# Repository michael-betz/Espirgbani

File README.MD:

# ESP Pinball RGB Animation clock

A LED-matrix clock, based on ESP32 and sprite_tm's I2S DMA driver.

__Note:__ 
the firmware here is outdated and will be removed in the future. 

[Espirgbani_pio](https://github.com/yetifrisstlama/espirgbani_pio) is up to date, has more features, less bugs, higher frame-rate and is much easier to build.

[Project log](http://yetifrisstlama.blogspot.com/2018/02/the-esp32-pinball-rgb-matrix-animation.html).

# PCB
Fits inside one of the 64x32 panels.

### Revisions
Changes included in Rev 1
  * Change programming port from custom pogo-pins to a normal header
  * Add input for ambient light level sensor
  * Re-arrange the mounting holes
  * Add second footprint for a uSD card

# Building
Unfortunately the projects which I based this software on are either completely obsolete or they moved on a lot. Building still works (as of April 2020) but only when using exactly the versions and git commits as specified below.

install [version 5.2.0 of `xtensa-esp32-elf` toolchain](https://dl.espressif.com/dl/xtensa-esp32-elf-linux64-1.22.0-80-g6c4433a-5.2.0.tar.gz) and put it in your `PATH`.

```bash
$ xtensa-esp32-elf-gcc --version
xtensa-esp32-elf-gcc (crosstool-NG crosstool-ng-1.22.0-80-g6c4433a) 5.2.0
Copyright (C) 2015 Free Software Foundation, Inc.
This is free software; see the source for copying conditions.  There is NO
warranty; not even for MERCHANTABILITY or FITNESS FOR A PARTICULAR PURPOSE.
```

install the esp-idf library.
```bash
git clone https://github.com/espressif/esp-idf.git
cd esp-idf
git checkout b173cf28174b17f7df96c298f83c16a00d22e312
git submodule init
git submodule update
cd components
git clone --recurse-submodules git@github.com:yetifrisstlama/libesphttpd.git
export IDF_PATH=<insert_path>/esp-idf
```

Clone Espirgbani, build and flash it ...

```bash
git clone git@github.com:yetifrisstlama/Espirgbani.git
cd Espirgbani/src
make
make flash     # program esp32 over serial port, hold the FLASH button!
make web-flash # program esp32 over wifi, set hostname in Makefile
```

## fast-seek
For a smoother animation playback, the fast-seek option needs to be enabled in
the fatfs library. Use the provided .patch file ...
```bash
cd esp-idf
patch -p1 -i ../Espirgbani/src/0001-Enable-FASTSEEK-option-in-FatFs.patch
```

# SD card instructions
Format as FAT32, then copy the following files:
  * `./settings.json`
  * `./runDmd.img`
  * `./fnt/{d}.fnt`
  * `./fnt/{d}_0.bmp`

## example `settings.json`
```json
{
    "panel": {
        "test_pattern": false,
        "tp_brightness":  10,
        "is_clk_inverted": true,
        "column_swap": false,
        "latch_offset": 0,
        "extra_blank": 1,
        "clkm_div_num": 4
    },
    "power": {
        "hi": {
            "h": 9,
            "m": 0,
            "p": 50,
            "pingIp": "192.168.1.208"
        },
        "lo": {
            "h": 22,
            "m": 45,
            "p": 1
        }
    },
    "delays": {
        "font":  60,
        "color": 10,
        "ani":   15,
        "ping":  60
    },
    "log_level": "W",
    "timezone": "PST8PDT,M3.2.0,M11.1.0",
    "hostname": "espirgbani",
    "wifis": {
        "<wifi-ssid>": {
            "pw": "<wifi-password>"
        }
    }
}
```
### `panel` section
Not all LED panels are the same. Here the timing parameters of the I2S panel driver can be configured.

  * `test_pattern`: if true, enters a LED panel test mode instead of normal operation
  * `tp_brightness`: brightness of the test pattern, from 1 to 127. Current draw gets ridiculous for the higher values
  * `is_clk_inverted`: if `false`, data changes on the rising clock edge. If `true`, data is stable on the rising clock edge (most panels need `true`)
  * `column_swap`: if true, swap each pair of vertical columns
  * when `latch_offset = 0`: latch row-data with last pixel. For positive / negative numbers the latching happens n clock cycles earlier / later. Shifts the image horizontally
  * `extra_blank` adds N additional delay cycles after latching before enabling the LEDs to prevent ghosting artifacts from one row to another
  * `clkm_div_num` sets the I2S clock divider from 1 to 128. Set it too high and get flicker,  too low get ghost pixels. `4` (= 8 MHz pixel clock) is a good compromise for my panels

### `power` section
controls the display brightness depending on current time.

  * Switches to brightness `90` at `9:00`
  * But only if `192.168.1.208` responds to pings
  * Switches to brightness `1` at `22:45`

### `delays` section
controls delays between random animations, color and font changes.

  * Changes the clock font every 60 minutes
  * Changes color of the clock font every 10 minutes
  * Plays a new pinball animation every 15 seconds
  * tries to ping `pingIp` every 60 seconds

### `log_level`
is the logging level for the serial port and the web-console on startup. Can be one of the following letters: `E = ERROR`, `W = WARN`, `I = INFO`, `D = DEBUG`, `V = VERBOSE`

### `timezone`
is the local timezone in [TZ format](https://www.gnu.org/software/libc/manual/html_node/TZ-Variable.html). Look it up [here](https://github.com/nayarsystems/posix_tz_db/blob/master/zones.csv).

Note that once running and connected to the wifi, the settings.json file can be edited through the web interface.

## how to get `runDmd.img`
  * Find a run-dmd image file and write it to SD card according to their instructions (HDD Raw Copy Tool and Windows required)
  * In linux, dump the first few hundred megabytes of the SD card to a file:
  ```bash
  sudo dd if=/dev/sdb of=./runDmd.img bs=1M count=125
  ```

## how to get the font `.bmp` and `.fnt` files
  * Find some nice fonts which look good at small size and copy the `.ttf` files into the git tree at `./dev/fonts`
  * Use [bmFont](http://www.angelcode.com/products/bmfont/) (works well with wine in linux) to generate the bitmap fonts. Good settings are provided in `dev/clockFont.bmfc`
    * Width: 52, Height: 2000
    * 32 bit per pixel (A = one, R = glyph, G = outline, B = zero)
    * .png texture file
    * binary .fnt descriptor file
    * Size: 30 px, Outline thickness: 1 px
  * Use imagemagick to convert all image files to bmp format
  * Rename them to 0_0.bmp, 0.fnt;  1_0.bmp, 1.fnt, ...
  * Alternatively, run `./dev/generateFonts.sh` which should automate these steps

## Pre-built binaries (TLDR!)
Prebuilt firmware binaries for the ESP32 and the files for the (FAT32) SD card are [here](https://github.com/yetifrisstlama/Espirgbani/releases/tag/v1.0).

# TODO
  * rewrite .json settings

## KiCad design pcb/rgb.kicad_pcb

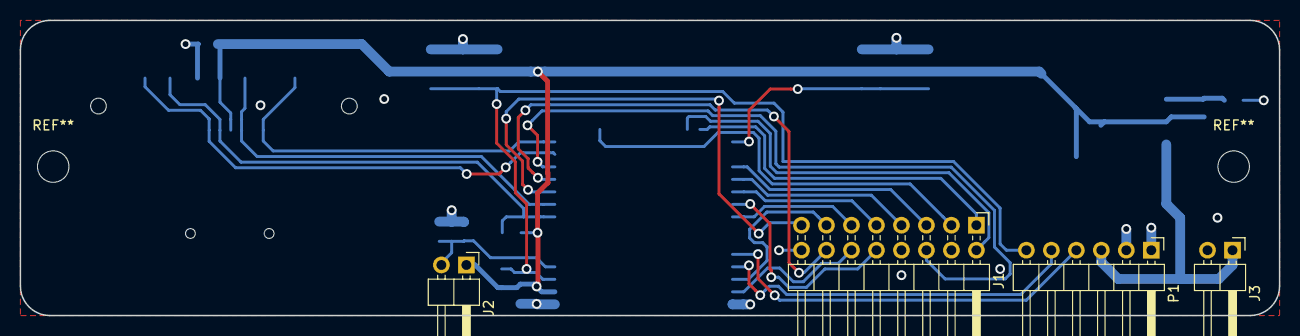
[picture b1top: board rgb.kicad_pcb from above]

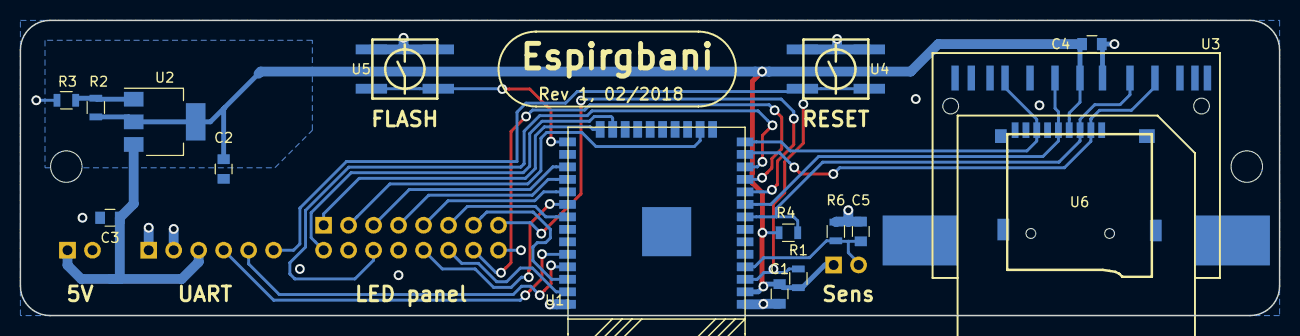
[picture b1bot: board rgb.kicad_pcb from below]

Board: 2 copper layers, 128.0 x 30.0 mm, 20 parts (16 on the bottom side), 26 nets.

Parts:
C1: 470n; C_0805
C2, C3, C4: 10u; C_0805
C5: 1u; C_0805
J1: Conn_02x08_Odd_Even; Pin_Header_Angled_2x08_Pitch2.54mm
J2, J3: Conn_01x02; Pin_Header_Angled_1x02_Pitch2.54mm
P1: TTL_232R_3V3; Pin_Header_Angled_1x06_Pitch2.54mm
R1: 470k; R_0805
R2: 590R; R_0805
R3: 1k; R_0805
R4, R6: 10k; R_0805
U1: ESP-WROOM-32
U2: REG1117; SOT-223
U3: 412D02F; RPIA_SD_CARD
U4, U5: TACTILE; EVQQ2
U6: MicroSD_SPI_CD; GCT-MEM2055-00-190-01-A

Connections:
+3V3: C1.2, C2.2, C4.1, J2.1, R1.1, R2.1, R4.2, U1.2, U2.2, U2.4, U3.7, U6.4
+5V: C3.2, J3.1, P1.3, U2.3
/A: J1.9, U1.29
/B: J1.10, U1.30
/B0: J1.3, U1.16
/B1: J1.7, U1.28
/C: J1.11, U1.31
/CLK: J1.13, U1.36
/D: J1.12, U1.37
/G0: J1.2, U1.23
/G1: J1.6, U1.12
/OE: J1.15, U1.10
/R0: J1.1, U1.24
/R1: J1.5, U1.27
/SD_CLK: U1.9, U3.8, U6.5
/SD_CS: U1.13, U3.4, U6.2
/SD_MISO: U1.14, U3.10, U6.7
/SD_MOSI: R4.1, U1.8, U3.5, U6.3
/STB: J1.14, U1.11
/progFlag: U1.25, U5.A, U5.A'
/rstBtn: P1.6, R1.2, U1.3, U4.A, U4.A'
GND: C1.1, C2.1, C3.1, C4.2, C5.2, J1.4, J1.8, J1.16, J3.2, P1.1, P1.2, R3.2, R6.2, U1.1, U1.15, U1.38, U1.39, U3.1, U3.2, U3.6, U3.9, U3.12, U3.13, U3.14, U3.15, U4.B, U4.B', U5.B, U5.B', U6.6
unnamed: C5.1, J2.2, R6.1, U1.4
unnamed: P1.4, U1.34
unnamed: P1.5, U1.35
unnamed: R2.2, R3.1, U2.1

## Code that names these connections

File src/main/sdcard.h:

#ifndef SDCARD_H
#define SDCARD_H

#define GPIO_SD_CLK  33
#define GPIO_SD_MOSI 32
#define GPIO_SD_MISO 12
#define GPIO_SD_CS   14

void initSd();

#endif

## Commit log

2017-11-30 Initial
2017-11-30 gitignore
2017-11-30 Readme
2017-12-01 Minimum example to show 1 (sub)frame for debugging
2017-12-03 First working version. MAtrix flickers when i2s clock si changed for bitplanes=7
2017-12-04 SD card is online and integrated into webserver
2017-12-04 Hmm sd card write bug?
2017-12-07 revengwork
2017-12-07 Got the gif extractor working
2017-12-08 Progress on file format
2017-12-08 offsets still a mystery
2017-12-08 Finally cracked the header offset
2017-12-08 c parser for header
2017-12-10 Finally cracked the header format with the correct offsets
2017-12-11 Animations osrtof working:
2017-12-23 played with bitmap fonts
2017-12-24 Added .fnt decoder
2017-12-25 Bitmapfonts :)
2017-12-26 Huge update! Strings! Fonts! Brightness! SLiders! Layersgit add src/main/font.* Awesomeness!
2017-12-26 Fine tuned
2018-01-16 Random fonts for the clock every hour
2018-01-22 Made background patterns more random
2018-01-25 ready for auto font
2018-01-26 Added font conversion shell script
2018-01-29 Real premultiplied alpha support. drawing over conten in framebuffer now possible. font outline works now. alternative background pattern
2018-01-31 Added outline AA (24 bit bmp). Font file counting on startup
2018-01-31 Removed font assets
2018-02-02 Added pics
2018-02-02 front
2018-02-10 Fixed colored backgrounds
2018-02-21 added json settings system
2018-02-22 Added the alien flame shader
2018-02-23 pinging my mobile to dim the display when Im not at home'
2018-02-25 PCB REV1
2018-02-25 Readme update
2018-02-25 PCB rev1 mostly finished but untested
2018-03-04 layout
2018-03-27 More vivd colors
2018-03-27 ping is now in ms
2018-03-28 final pcb with second sd card slot and kicad 5
2018-04-21 Cosmetic improvements.
2018-05-06 align fonts better, make delays configurabel
2018-05-11 Fix compiler warning by adding const char
2018-05-11 Flash button = Hotspot mode, print status on leds
2018-05-11 Add fatfs patch for esp-idf and compiled .bin file
2018-05-11 No ping on empty IP string
2018-08-04 Make number of bad pings configurable
2018-12-17 update PCB pictures
2018-12-17 Fix dmd2gif.py
2018-12-17 slight cleanup
2018-12-17 remove a large text file
2018-12-17 SD image
2019-01-12 Add doom flame effect
    inspired by http://fabiensanglard.net/doom_fire_psx/
2019-01-13 Update to latest esp-idf
    * README.MD Add notes about building
    * Add many palettes for fire effect
    * Add new fast-seek patch
2019-01-13 README: minor stuff
2019-01-14 web_console: default log level = warning
2019-01-15 Tried to fix startuptrouble
2020-03-12 pcb: fix value of V-REG, Add info about SD card sockets
2020-04-14 update build instructions, add .json timezone setting
2020-04-17 remove redundant .dxf files
2020-06-01 i2s_parallel.c: undid changes to spritetm's code
2020-06-01 add bin folder for make espirgbani.zip
2020-06-01 enabled flicker hack
2020-06-01 clean up Makefiel
2020-06-01 fix 1 pixel x-offset
2020-06-01 seed the RNG
2020-06-04 make panel settings configurablei
    also invert clk signal
2020-06-04 work in progress
2020-06-04 improve .json configuration
    * rgb panel driver can now be parametrized
    * this includes polarity of the clock signal, which was wrong before!
    * add test-pattern mode
    * make file handling much more robust. Starts up without SD card.
2020-06-12 pcb: clean up project. Make kicad 5.1.x compatible
2020-06-12 pcb: re-save without copper zones
2020-06-13 update font generation script
    .. add setting for custom font_size for each .ttf file
2020-06-14 add more font sources
2020-06-14 generateFonts.sh: 2 digit filenames, fix some bugs
2020-06-14 generateFonts.sh: fine-tuned font-sizes
2020-06-15 fine tune font sizes
